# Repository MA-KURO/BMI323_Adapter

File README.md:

# BMI323_Adapter
BMI323转接板，SPI接口

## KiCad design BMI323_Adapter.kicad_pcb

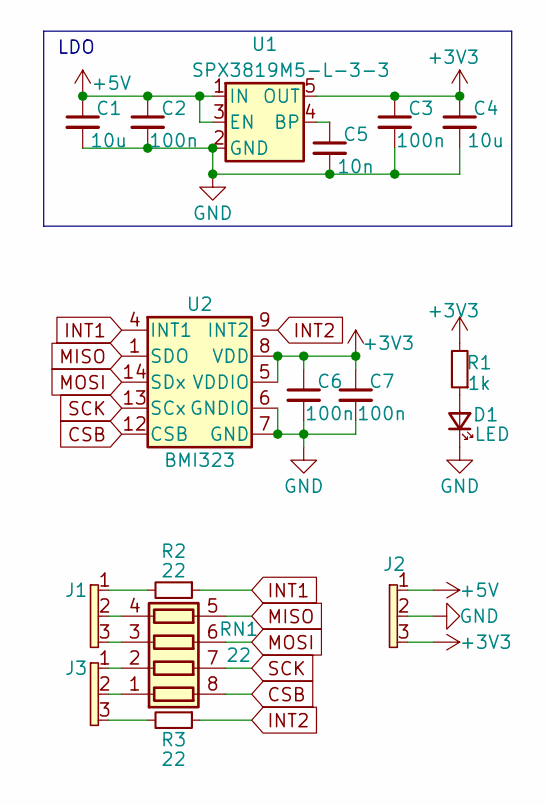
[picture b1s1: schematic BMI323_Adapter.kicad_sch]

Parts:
C1, C4: 10u; 0603_C
C2, C3, C6, C7: 100n; 0603_C
C5: 10n; 0603_C
D1: LED; 0603_D
J1, J2, J3: Conn_01x03_Pin_N; PinHeader_1x03_P2.54mm_Vertical
R1: 1k; 0603_R
R2, R3: 22; 0603_R
RN1: 22; 0603_RX4
U1: SPX3819M5-L-3-3; SOT-23-5
U2: BMI323; Bosch_LGA-14_3x2.5mm_P0.5mm

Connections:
+3V3: C3.1, C4.1, C6.1, C7.1, J2.3, R1.2, U1.5 (OUT), U2.5 (VDDIO), U2.8 (VDD)
+5V: C1.1, C2.1, J2.1, U1.1 (IN), U1.3 (EN)
CSB: RN1.8 (R1.2), U2.12 (CSB)
GND: C1.2, C2.2, C3.2, C4.2, C5.2, C6.2, C7.2, D1.2 (K), J2.2, U1.2 (GND), U2.6 (GNDIO), U2.7 (GND)
INT1: R2.1, U2.4 (INT1)
INT2: R3.1, U2.9 (INT2)
MISO: RN1.5 (R4.2), U2.1 (SDO)
MOSI: RN1.6 (R3.2), U2.14 (SDx)
unnamed: D1.1 (A), R1.1
unnamed: J1.1, R2.2
unnamed: J3.3, R3.2
unnamed: J3.2, RN1.1 (R1.1)
unnamed: J3.1, RN1.2 (R2.1)
unnamed: J1.3, RN1.3 (R3.1)
unnamed: J1.2, RN1.4 (R4.1)
unnamed: C5.1, U1.4 (BP)
SCK: RN1.7 (R2.2), U2.13 (SCx)

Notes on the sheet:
LDO

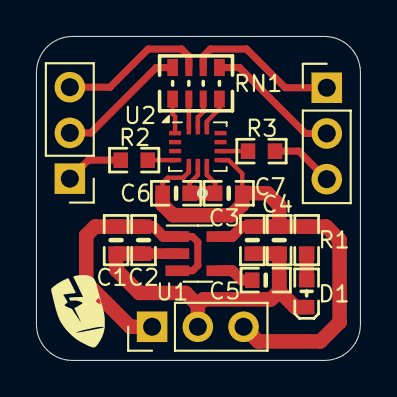
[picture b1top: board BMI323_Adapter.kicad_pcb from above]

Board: 2 copper layers, 18.0 x 18.0 mm, 17 parts (0 on the bottom side), 17 nets.

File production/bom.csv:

Designator,Footprint,Quantity,Value,LCSC Part #
"C1, C4",0603_C,2,10u,
"C2, C3, C6, C7",0603_C,4,100n,
C5,0603_C,1,10n,
D1,0603_D,1,LED,
"J1, J2, J3",PinHeader_1x03_P2.54mm_Vertical,3,Conn_01x03_Pin_N,
R1,0603_R,1,1k,
"R2, R3",0603_R,2,22,
RN1,0603_RX4,1,22,
U1,SOT-23-5,1,SPX3819M5-L-3-3,
U2,Bosch_LGA-14_3x2.5mm_P0.5mm,1,BMI323,

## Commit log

2024-06-24 第一次提交
2024-06-24 第一次上传
2024-07-08 制造输出
